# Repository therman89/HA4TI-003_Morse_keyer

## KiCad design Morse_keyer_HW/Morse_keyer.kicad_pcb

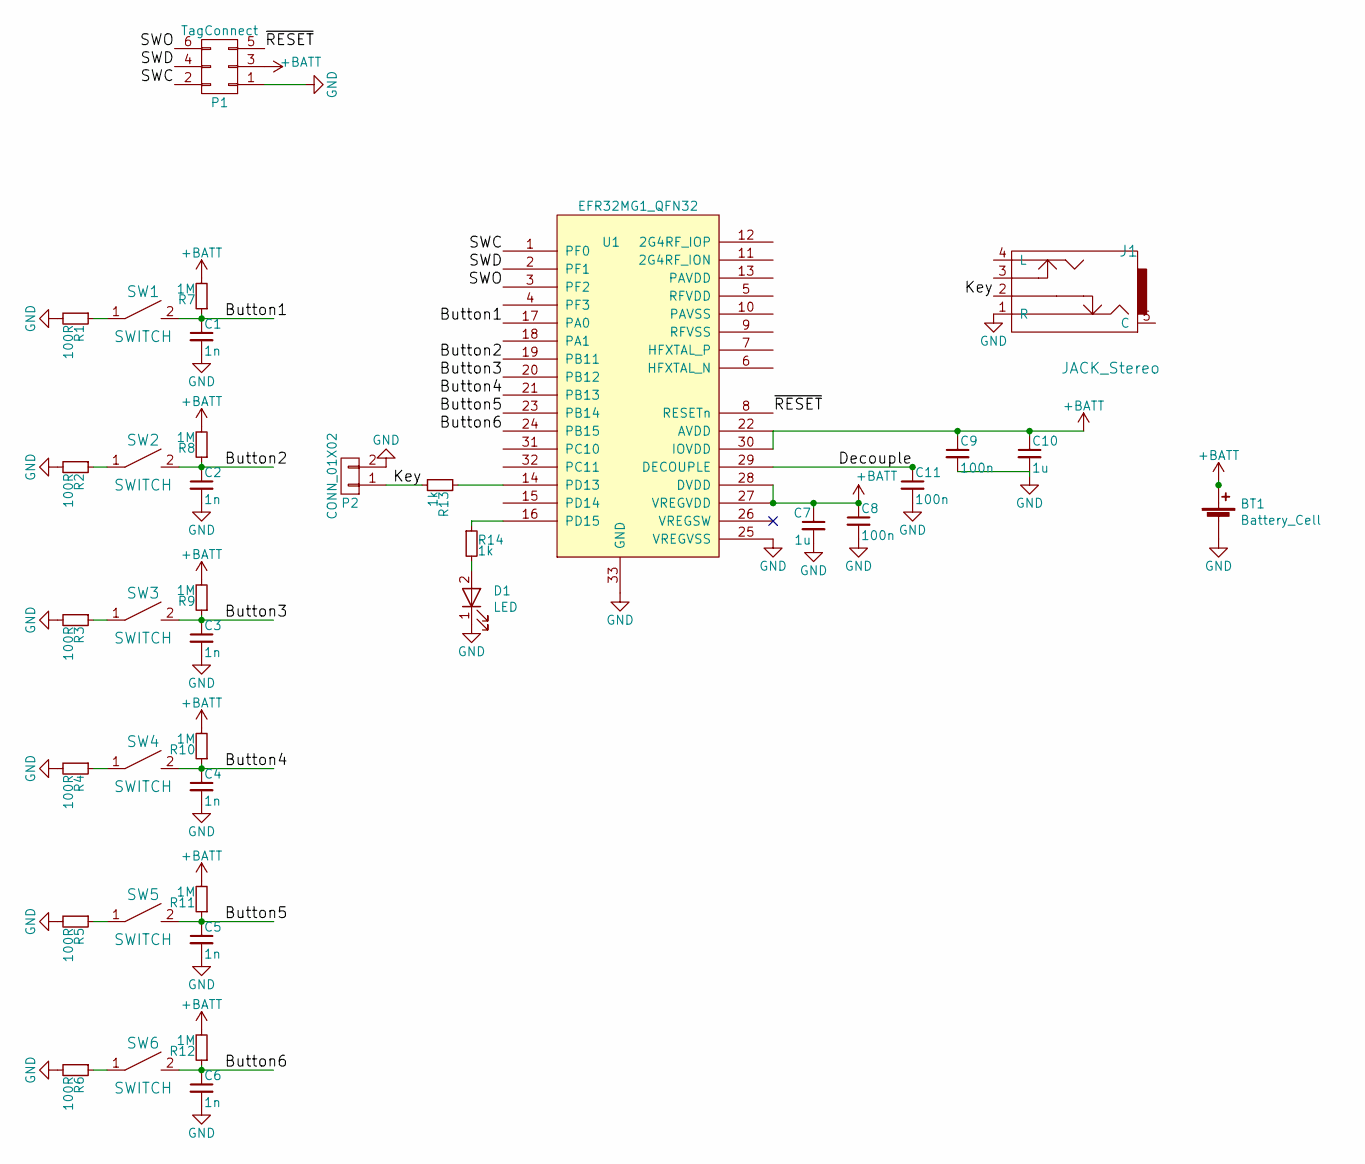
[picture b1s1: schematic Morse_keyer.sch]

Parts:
BT1: Battery_Cell; CR2032_holder
C1, C2, C3, C4, C5, C6: 1n; C_0603
C7, C10: 1u; C_0603
C8, C9, C11: 100n; C_0603
D1: LED; LED_0603
J1: JACK_Stereo; AudioJack3.5mm_stereo
P1: TagConnect; Tag-Connect_TC2030-IDC-NL
P2: CONN_01X02; Pin_Header_Straight_1x02_Pitch2.00mm
R1, R2, R3, R4, R5, R6: 100R; R_0603_HandSoldering
R7, R8, R9, R10, R11, R12: 1M; R_0603_HandSoldering
R13, R14: 1k; R_0603_HandSoldering
SW1, SW2, SW3, SW4, SW5, SW6: SWITCH; SPST-4-PIN_6mm_sm
U1: EFR32MG1_QFN32; QFN-32-1EP_5x5mm_Pitch0.5mm

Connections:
+BATT: BT1.1 (+), C7.1, C8.1, C9.1, C10.1, P1.3, R7.2, R8.2, R9.2, R10.2, R11.2, R12.2, U1.22 (AVDD), U1.27 (VREGVDD), U1.28 (DVDD), U1.30 (IOVDD)
/Button1: C1.1, R7.1, SW1.2, U1.17 (PA0)
/Button2: C2.1, R8.1, SW2.2, U1.19 (PB11)
/Button3: C3.1, R9.1, SW3.2, U1.20 (PB12)
/Button4: C4.1, R10.1, SW4.2, U1.21 (PB13)
/Button5: C5.1, R11.1, SW5.2, U1.23 (PB14)
/Button6: C6.1, R12.1, SW6.2, U1.24 (PB15)
/Decouple: C11.1, U1.29 (DECOUPLE)
/Key: J1.2, P2.1, R13.2
/SWC: P1.2, U1.1 (PF0)
/SWD: P1.4, U1.2 (PF1)
/SWO: P1.6, U1.3 (PF2)
/~RESET: P1.5, U1.8 (RESETn)
GND: BT1.2 (-), C1.2, C2.2, C3.2, C4.2, C5.2, C6.2, C7.2, C8.2, C9.2, C10.2, C11.2, D1.1 (K), J1.1 (R), P1.1, P2.2, R1.2, R2.2, R3.2, R4.2, R5.2, R6.2, U1.25 (VREGVSS), U1.33 (GND)
unnamed: D1.2 (A), R14.2
unnamed: R1.1, SW1.1
unnamed: R2.1, SW2.1
unnamed: R3.1, SW3.1
unnamed: R4.1, SW4.1
unnamed: R5.1, SW5.1
unnamed: R6.1, SW6.1
unnamed: R13.1, U1.14 (PD13)
unnamed: R14.1, U1.16 (PD15)

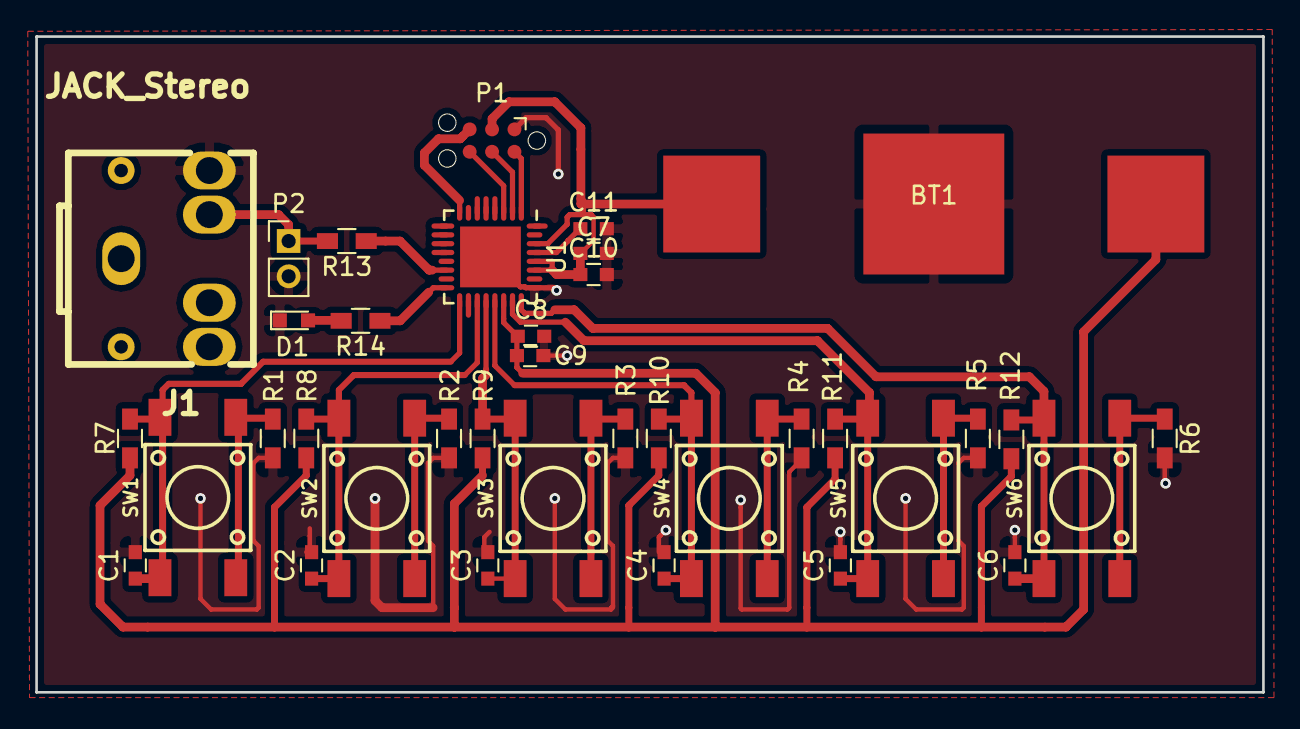
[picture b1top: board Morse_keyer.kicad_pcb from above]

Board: 2 copper layers, 69.6 x 37.2 mm, 37 parts (0 on the bottom side), 23 nets.

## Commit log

2017-03-02 Initial commit with schematic and layout
2017-04-21 gitignore update
2017-04-21 Changed chip to QFN32 EFR32MG1
2017-04-25 Changed to QFN32 package EFR32MG1
